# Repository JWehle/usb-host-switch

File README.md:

# usb-host-switch
Simple 2-way switch for a USB device to switch it between two different hosts.

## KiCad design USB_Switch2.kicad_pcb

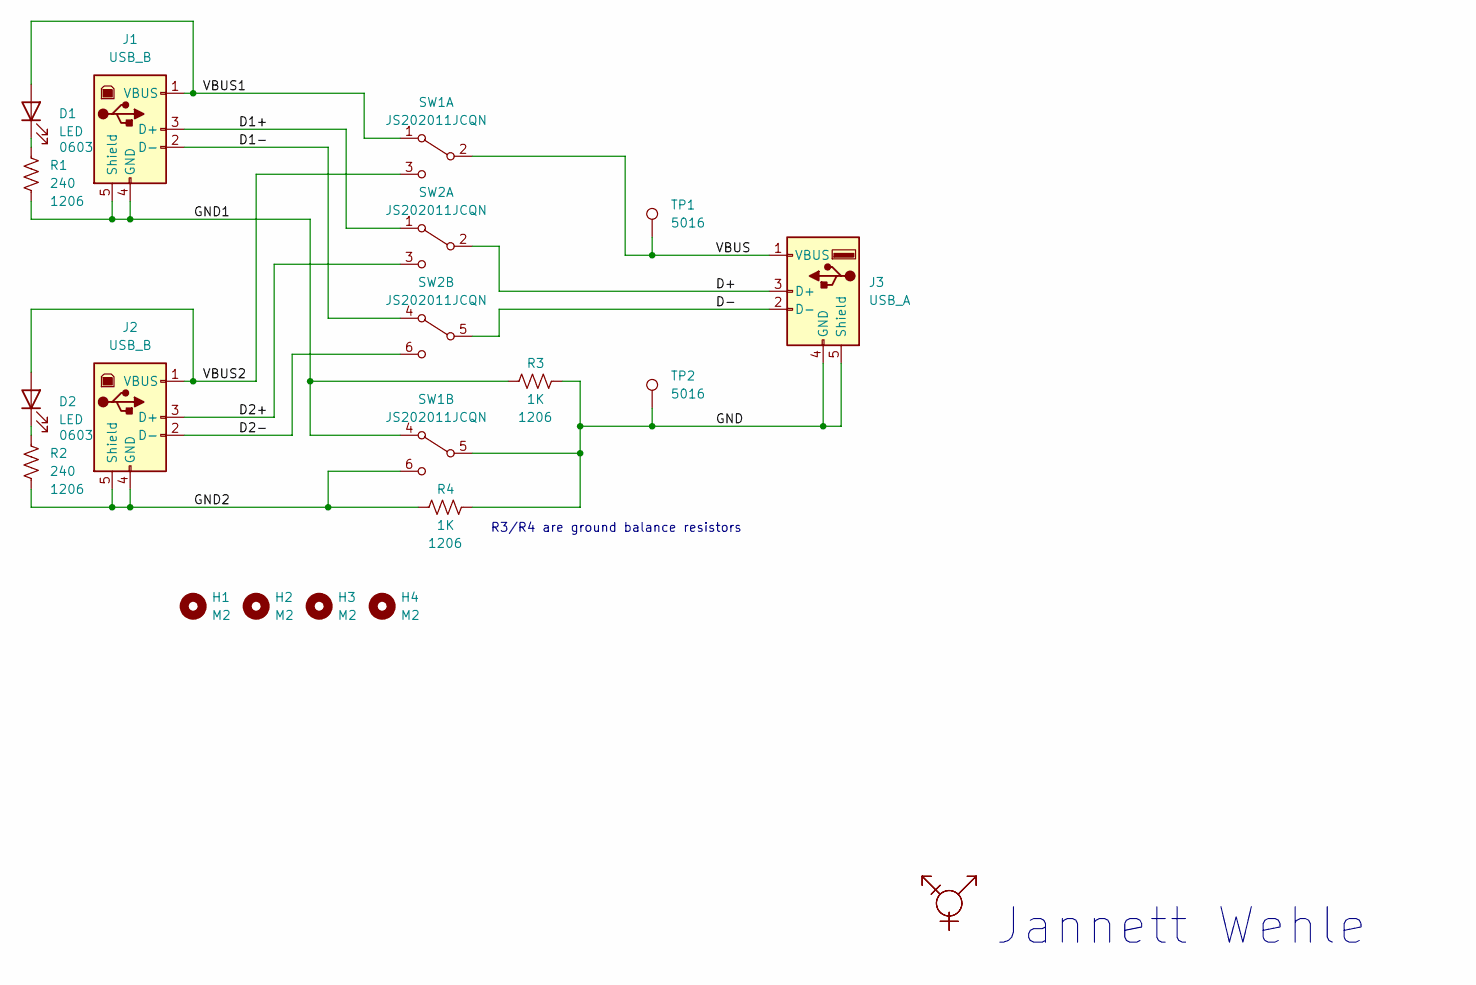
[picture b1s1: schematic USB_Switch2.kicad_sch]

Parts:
D1, D2: LED; LED_0603_1608Metric_Pad1.05x0.95mm_HandSolder
H1, H2, H3, H4: M2; MountingHole_2.2mm_M2
J1, J2: USB_B; USB_B_OST_USB-B1HSxx_Horizontal
J3: USB_A; USB_A_Molex_67643_Horizontal
R1, R2: 240; R_1206_3216Metric
R3, R4: 1K; R_1206_3216Metric
SW1, SW2: JS202011JCQN; SW_DPDT_CK_JS202011JCQN
SYMBOL1, SYMBOL2: Trans_Symbol
TP1, TP2: 5016; TestPoint_Keystone_5016_Compact

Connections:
/D1+: J1.3 (D+), SW2.1 (A)
/D1-: J1.2 (D-), SW2.4 (A)
/D2+: J2.3 (D+), SW2.3 (C)
/D2-: J2.2 (D-), SW2.6 (C)
/D+: J3.3 (D+), SW2.2 (B)
/D-: J3.2 (D-), SW2.5 (B)
/GND: J3.4 (GND), J3.5 (Shield), R3.2, R4.2, SW1.5 (B), TP2.1
/GND1: J1.4 (GND), J1.5 (Shield), R1.2, R3.1, SW1.4 (A)
/GND2: J2.4 (GND), J2.5 (Shield), R2.2, R4.1, SW1.6 (C)
/VBUS: J3.1 (VBUS), SW1.2 (B), TP1.1
/VBUS1: D1.2 (A), J1.1 (VBUS), SW1.1 (A)
/VBUS2: D2.2 (A), J2.1 (VBUS), SW1.3 (C)
unnamed: D1.1 (K), R1.1
unnamed: D2.1 (K), R2.1

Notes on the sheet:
Jannett Wehle
R3/R4 are ground balance resistors

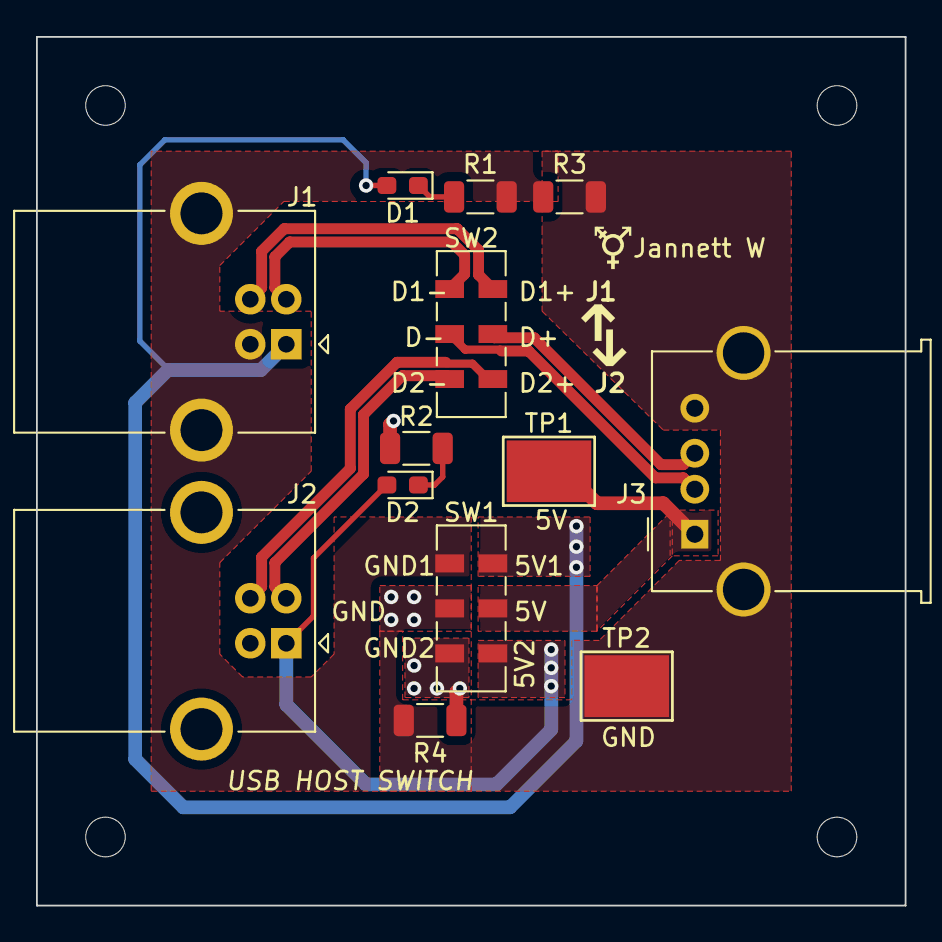
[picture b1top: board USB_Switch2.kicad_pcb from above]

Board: 2 copper layers, 48.3 x 48.3 mm, 19 parts (1 on the bottom side), 14 nets.
